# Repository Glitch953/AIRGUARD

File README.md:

# AIRGUARD

A portable, privacy-focused Wi-Fi environment analyzer based on the ESP32-S3. AIRGUARD scans nearby Wi-Fi networks using the ESP32-S3 MicroPython WLAN API and displays network metadata (SSID, channel, RSSI and security type) on an SSD1306 OLED. The current WLAN.scan() implementation is not verified as passive-only.

## Project status

This repository is a **design-stage prototype package**, not a validated manufacturing release. The KiCad source files are included for review and continued development. The PCB copper layout has not been rerouted in this package, and no KiCad ERC/DRC validation or hardware test is claimed.

The Gerber and drill files in `hardware/reference_gerbers_unmodified/` are copied from the original export and are provided for historical reference only. **They do not represent a newly revised PCB and must not be sent for fabrication as the final design.** Generate fresh fabrication outputs from the reviewed final KiCad board after electrical and mechanical checks.

## Repository layout

- `hardware/kicad/` — editable KiCad PCB, schematic and project source.
- `hardware/bom/` — minimal prototype BOM and placement list; verify manufacturer part numbers, quantities and sourcing before ordering.
- `hardware/reference_gerbers_unmodified/` — unchanged original Gerber/drill export for reference only.
- `firmware/micropython/` — initial MicroPython firmware and SSD1306 driver.
- `docs/` — revision status and assembly/firmware cautions.

## Firmware

The firmware uses MicroPython on ESP32-S3. It performs passive Wi-Fi scanning only; it does not connect to networks, capture passwords, transmit deauthentication frames, or jam networks. The pin map is a design assumption and must be checked against the assembled hardware before use.

## Important hardware cautions

- R7 and U3 are marked DNP in the prototype assembly notes. Do not populate them as-is.
- The buzzer output needs a suitable transistor/MOSFET driver before a buzzer is connected; do not drive the magnetic buzzer directly from an ESP32 GPIO.
- Confirm the OLED I2C pin mapping and all power/USB connections against the final schematic and datasheets.
- GPIO3 is a boot-strapping pin; avoid holding its button during reset/boot.

## Validation status

- KiCad ERC: not run.
- KiCad PCB DRC: not run.
- Gerber regeneration from this source: not performed.
- Physical assembly and firmware test: not performed; components are not yet available.

## License

Add a license before accepting external contributions or reuse.

## Procurement / Build status
- One-unit purchasing list: `docs/PURCHASE_LIST_AR.md` (Arabic) and `docs/PURCHASE_LIST_EN.md` (English).
- Structured purchasing BOM with quantities, indicative prices, purposes and store links: `hardware/bom/PURCHASE_BOM_AIRGUARD.csv`.
- OLED module is an additional purchase item; the original BOM listed only its PCB header.
- PCB manufacturing is **not yet authorized**: files in `hardware/reference_gerbers_unmodified/` are old reference exports and must not be sent to a board house. See `docs/REVISION_STATUS.txt`.

## Latest engineering preflight (Rev D)

See `docs/ENGINEERING_REVIEW_REV_D_PREFLIGHT.md` and `docs/OLED_WIRING_AR.md`. Schematic values were normalized, OLED wiring order was clarified, and the firmware documentation no longer claims passive-only scanning. The PCB copper routing is unchanged and the reference Gerbers are still not approved for fabrication.

## Hardware Design

### 3D Model

### PCB Layout

### Schematic

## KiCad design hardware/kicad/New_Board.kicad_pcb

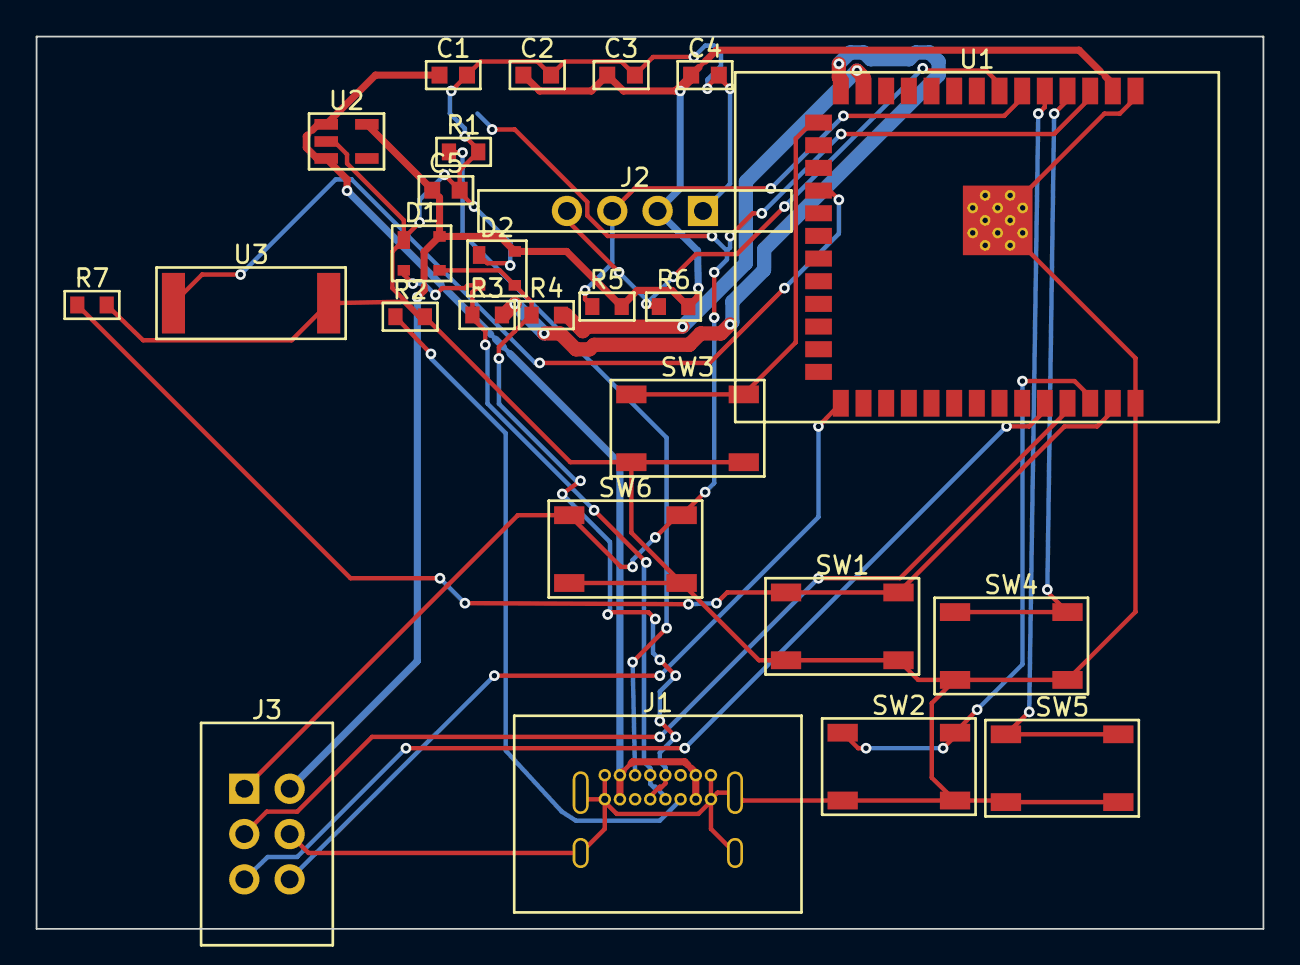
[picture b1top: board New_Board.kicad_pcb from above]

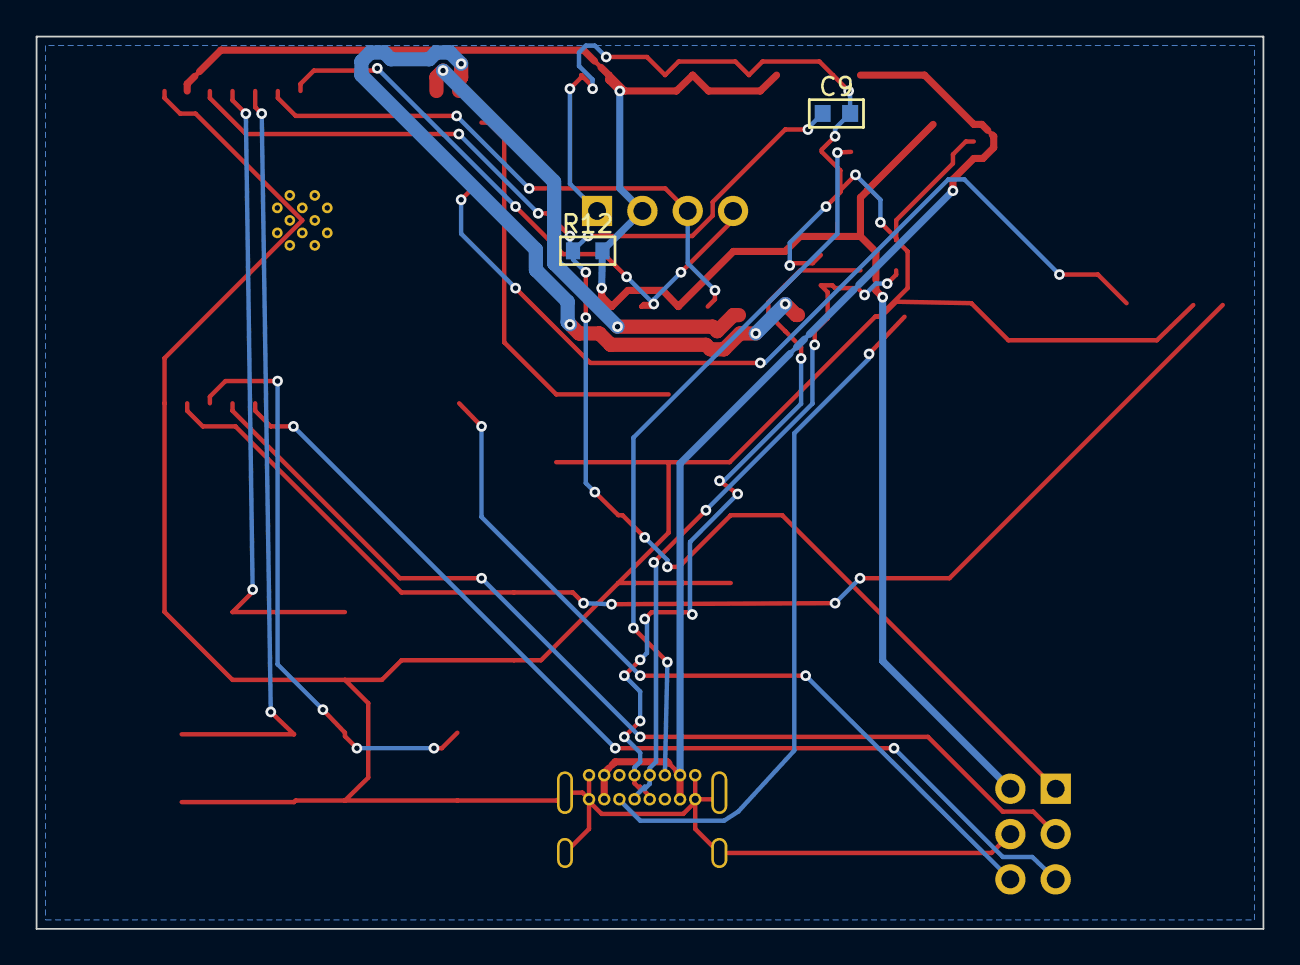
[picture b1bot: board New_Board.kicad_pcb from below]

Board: 2 copper layers, 68.8 x 50.0 mm, 28 parts (2 on the bottom side), 21 nets.

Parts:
C1, C2: 10uF; C_0603_1608Metric
C3, C4, C5: 0.1uF; C_0603_1608Metric
C9: 1uF; C_0603_1608Metric
D1, D2: PRTR5V0U2X,215; SOT-143
J1: USB4085-GF-A; USB_C_Receptacle_GCT_USB4085
J2: OLED Header; PinHeader_1x04_P2.54mm_Vertical
J3: Conn_02x03_Odd_Even; PinHeader_2x03_P2.54mm_Vertical
R1, R2: 5.1k; R_0603_1608Metric
R3, R4: 22; R_0603_1608Metric
R5, R6, R7: 4.7k; R_0603_1608Metric
R12: 10k; R_0603_1608Metric
SW1, SW2, SW3, SW4, SW5, SW6: SKRPACE010; SW_SPST_TL3342
U1: ESP32-S3-WROOM-1-N8; ESP32-S3-WROOM-1
U2: AP2112K-3.3TRG1; SOT-23-5
U3: CMT-8540S-SMT-TR; Buzzer_Murata_PKMCS0909E

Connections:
3V3: C2.1, C3.1, C4.1, C5.1, D1.4, D2.4, J2.2, J3.2, R5.2, R6.2, R12.2, U1.2 (3V3), U2.5 (VOUT)
BOOT: J3.6, U1.27 (IO0)
BUZZER_DRV: U1.18 (IO10), U3.1 (+)
CC1: J1.A5, R1.1
CC2: J1.B5, R2.1
EN: C9.1, J3.1, R12.1, SW6.1, U1.3 (EN)
GND: C1.2, C2.2, C3.2, C4.2, C5.2, C9.2, D1.1, D2.1, J1.A1, J1.A12, J1.B1, J1.B12, J1.SH, J2.1, J3.4, R1.2, R2.2, R7.2, SW1.2, SW2.2, SW3.2, SW4.2, SW5.2, SW6.2, U1.1 (GND), U1.40 (GND), U1.41 (GND), U2.2 (GND), U3.2 (-)
GPIO1: R7.1, SW1.1, U1.39 (IO1)
GPIO2: SW2.1, U1.38 (IO2)
GPIO3: SW3.1, U1.15 (IO3)
GPIO4: SW4.1, U1.4 (IO4)
GPIO5: SW5.1, U1.5 (IO5)
SCL: J2.4, R6.1, U1.7 (IO7)
SDA: J2.3, R5.1, U1.6 (IO6)
UART_RX: J3.5, U1.36 (RXD0)
UART_TX: J3.3, U1.37 (TXD0)
USB_DM: R4.2, U1.13 (USB_D-)
USB_DM_CONN: D1.3, D2.3, J1.A7, J1.B7, R4.1
USB_DP: R3.2, U1.14 (USB_D+)
USB_DP_CONN: D1.2, D2.2, J1.A6, J1.B6, R3.1
VBUS: C1.1, J1.A4, J1.A9, J1.B4, J1.B9, U2.1 (VIN), U2.3 (EN)

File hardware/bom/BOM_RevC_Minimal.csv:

Item,Quantity,Value,Footprint,Designators,LCSC,Mouser,Digi-Key,Manufacturer Part #,MOQ,Lifecycle,Description
1,1,ESP32-S3-WROOM-1-N8,RF_Module:ESP32-S3-WROOM-1,U1,,,,ESP32-S3-WROOM-1-N8,,,
2,1,USB4085-GF-A,Connector_USB:USB_C_Receptacle_GCT_USB4085,J1,,,,USB4085-GF-A,,,USB-C
3,1,AP2112K-3.3TRG1,Package_TO_SOT_SMD:SOT-23-5,U2,,,,AP2112K-3.3TRG1,,,3.3V 600mA
4,2,10uF,Capacitor_SMD:C_0603_1608Metric,"C1,C2",,,,,,,
5,3,0.1uF,Capacitor_SMD:C_0603_1608Metric,"C3,C4,C5",,,,,,,
6,2,5.1k,Resistor_SMD:R_0603_1608Metric,"R1,R2",,,,,,,
7,2,22,Resistor_SMD:R_0603_1608Metric,"R3,R4",,,,,,,
8,2,"PRTR5V0U2X,215",Package_TO_SOT_SMD:SOT-143,"D1,D2",,,,"PRTR5V0U2X,215",,,ESD diode
9,1,OLED Header,Connector_PinHeader_2.54mm:PinHeader_1x04_P2.54mm_Vertical,J2,,,,,,,
10,2,4.7k,Resistor_SMD:R_0603_1608Metric,"R5,R6",,,,,,,
11,6,SKRPACE010,Button_Switch_SMD:SW_SPST_TL3342,"SW1,SW2,SW3,SW4,SW5,SW6",,,,SKRPACE010,,,Tactile
13,1,Conn_02x03_Odd_Even,Connector_PinHeader_2.54mm:PinHeader_2x03_P2.54mm_Vertical,J3,,,,Conn_02x03_Odd_Even,,,Debug Header
14,1,10k,Resistor_SMD:R_0603_1608Metric,R12,,,,,,,
15,1,1uF,Capacitor_SMD:C_0603_1608Metric,C9,,,,,,,
